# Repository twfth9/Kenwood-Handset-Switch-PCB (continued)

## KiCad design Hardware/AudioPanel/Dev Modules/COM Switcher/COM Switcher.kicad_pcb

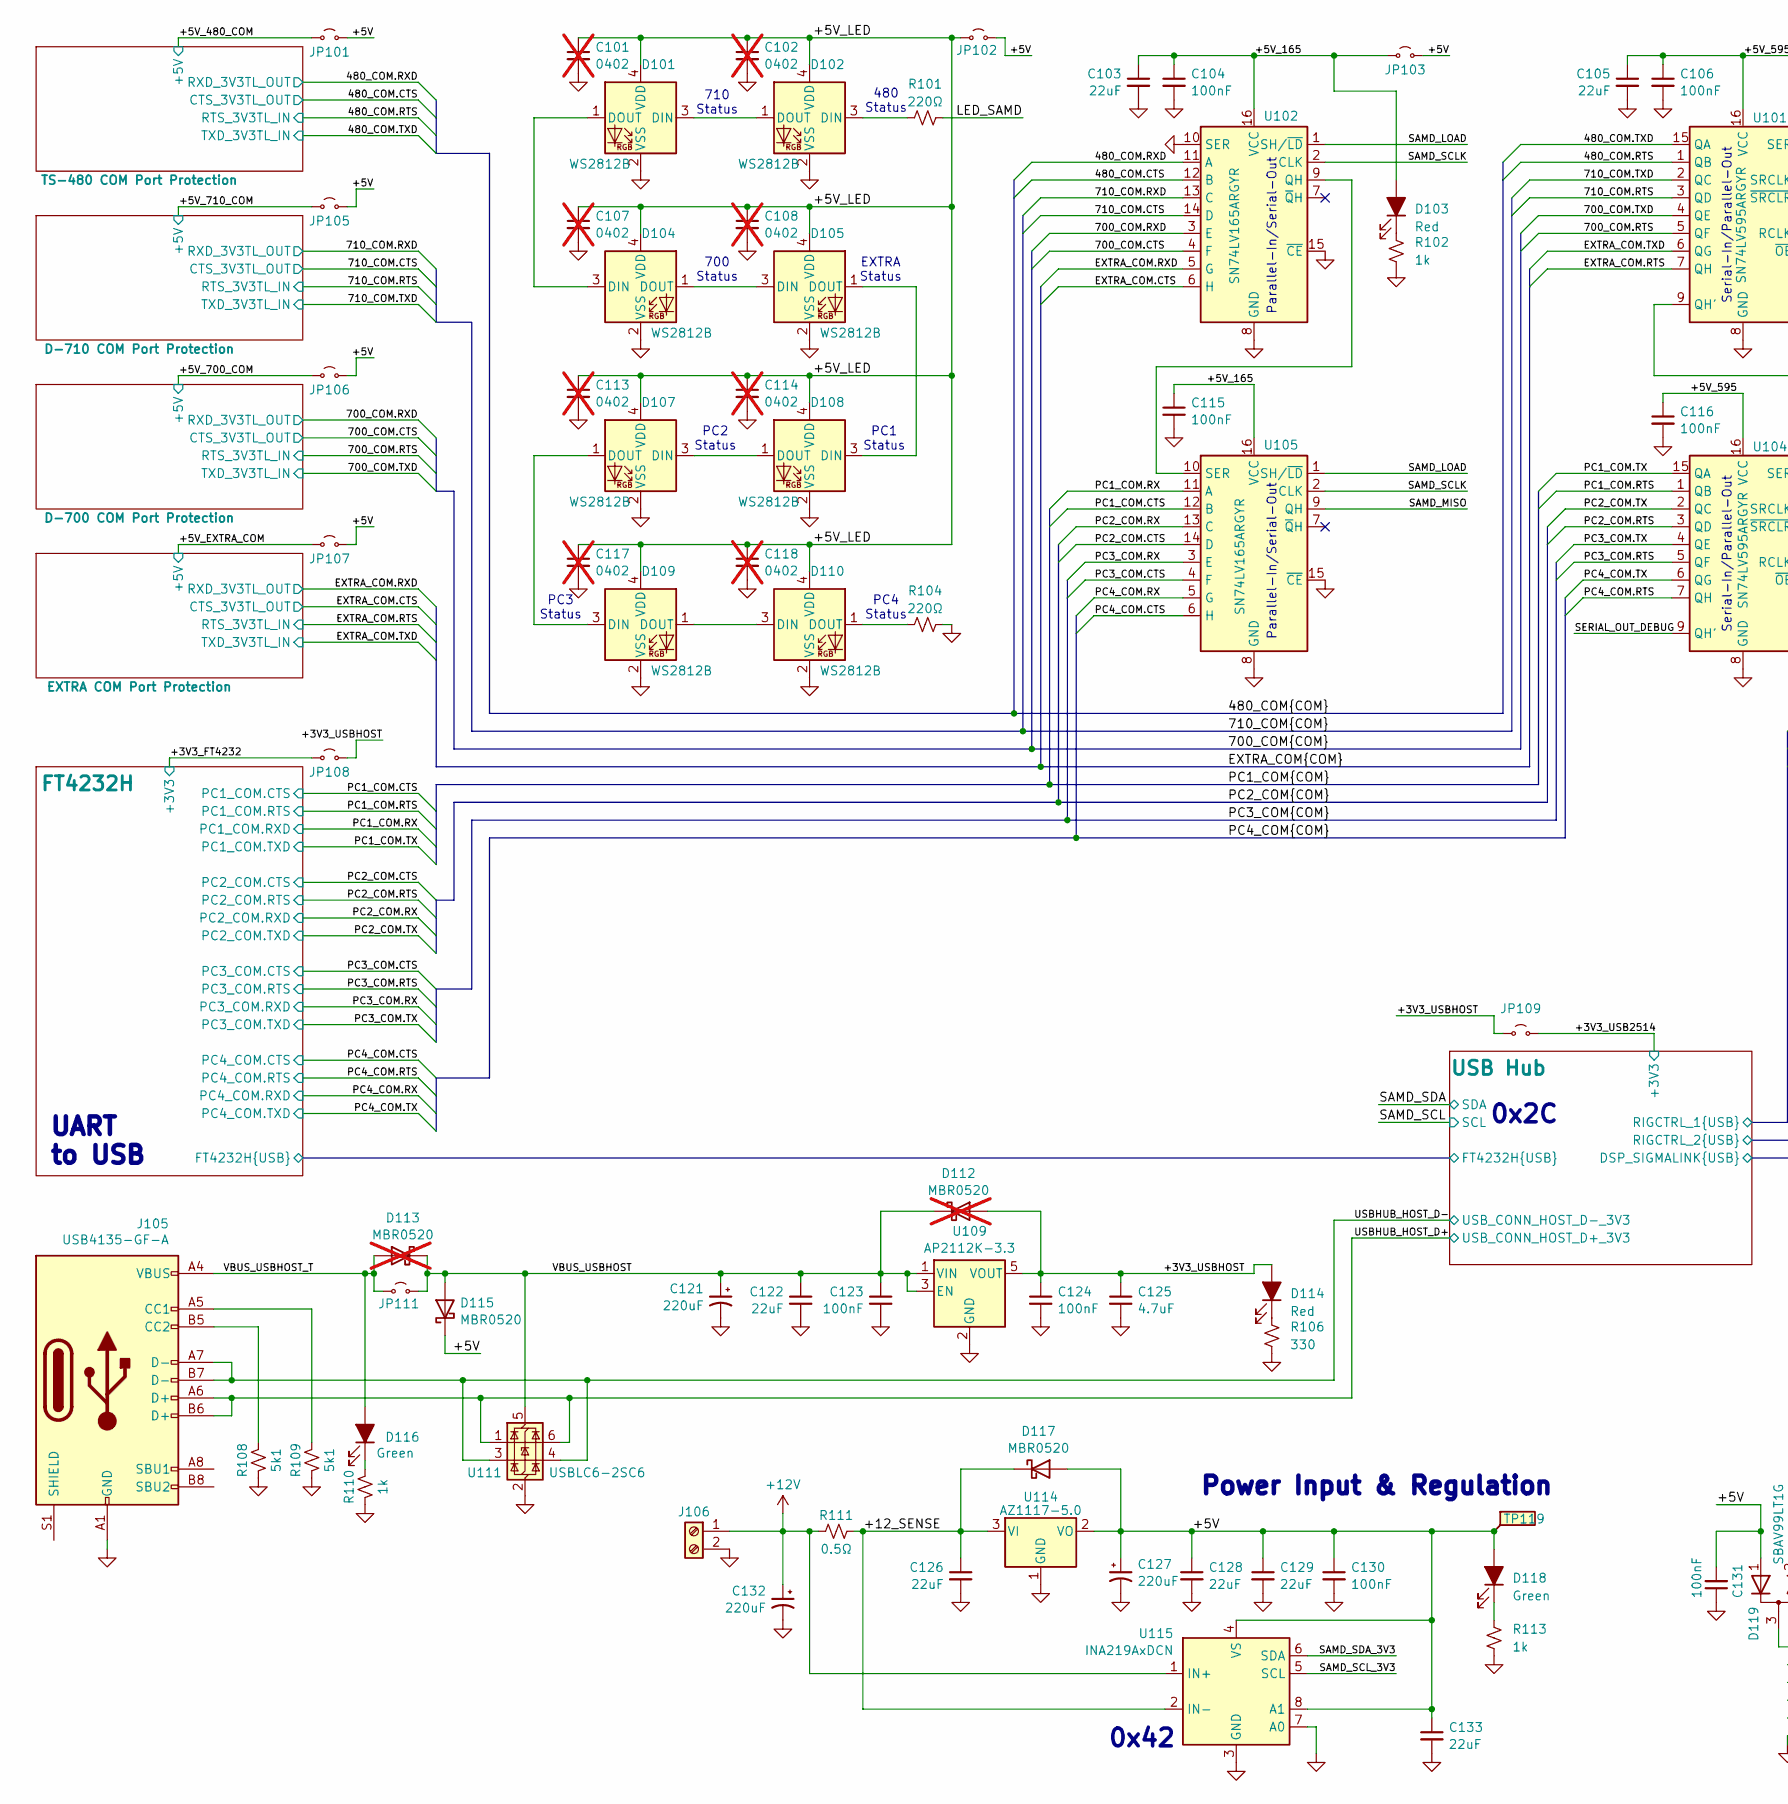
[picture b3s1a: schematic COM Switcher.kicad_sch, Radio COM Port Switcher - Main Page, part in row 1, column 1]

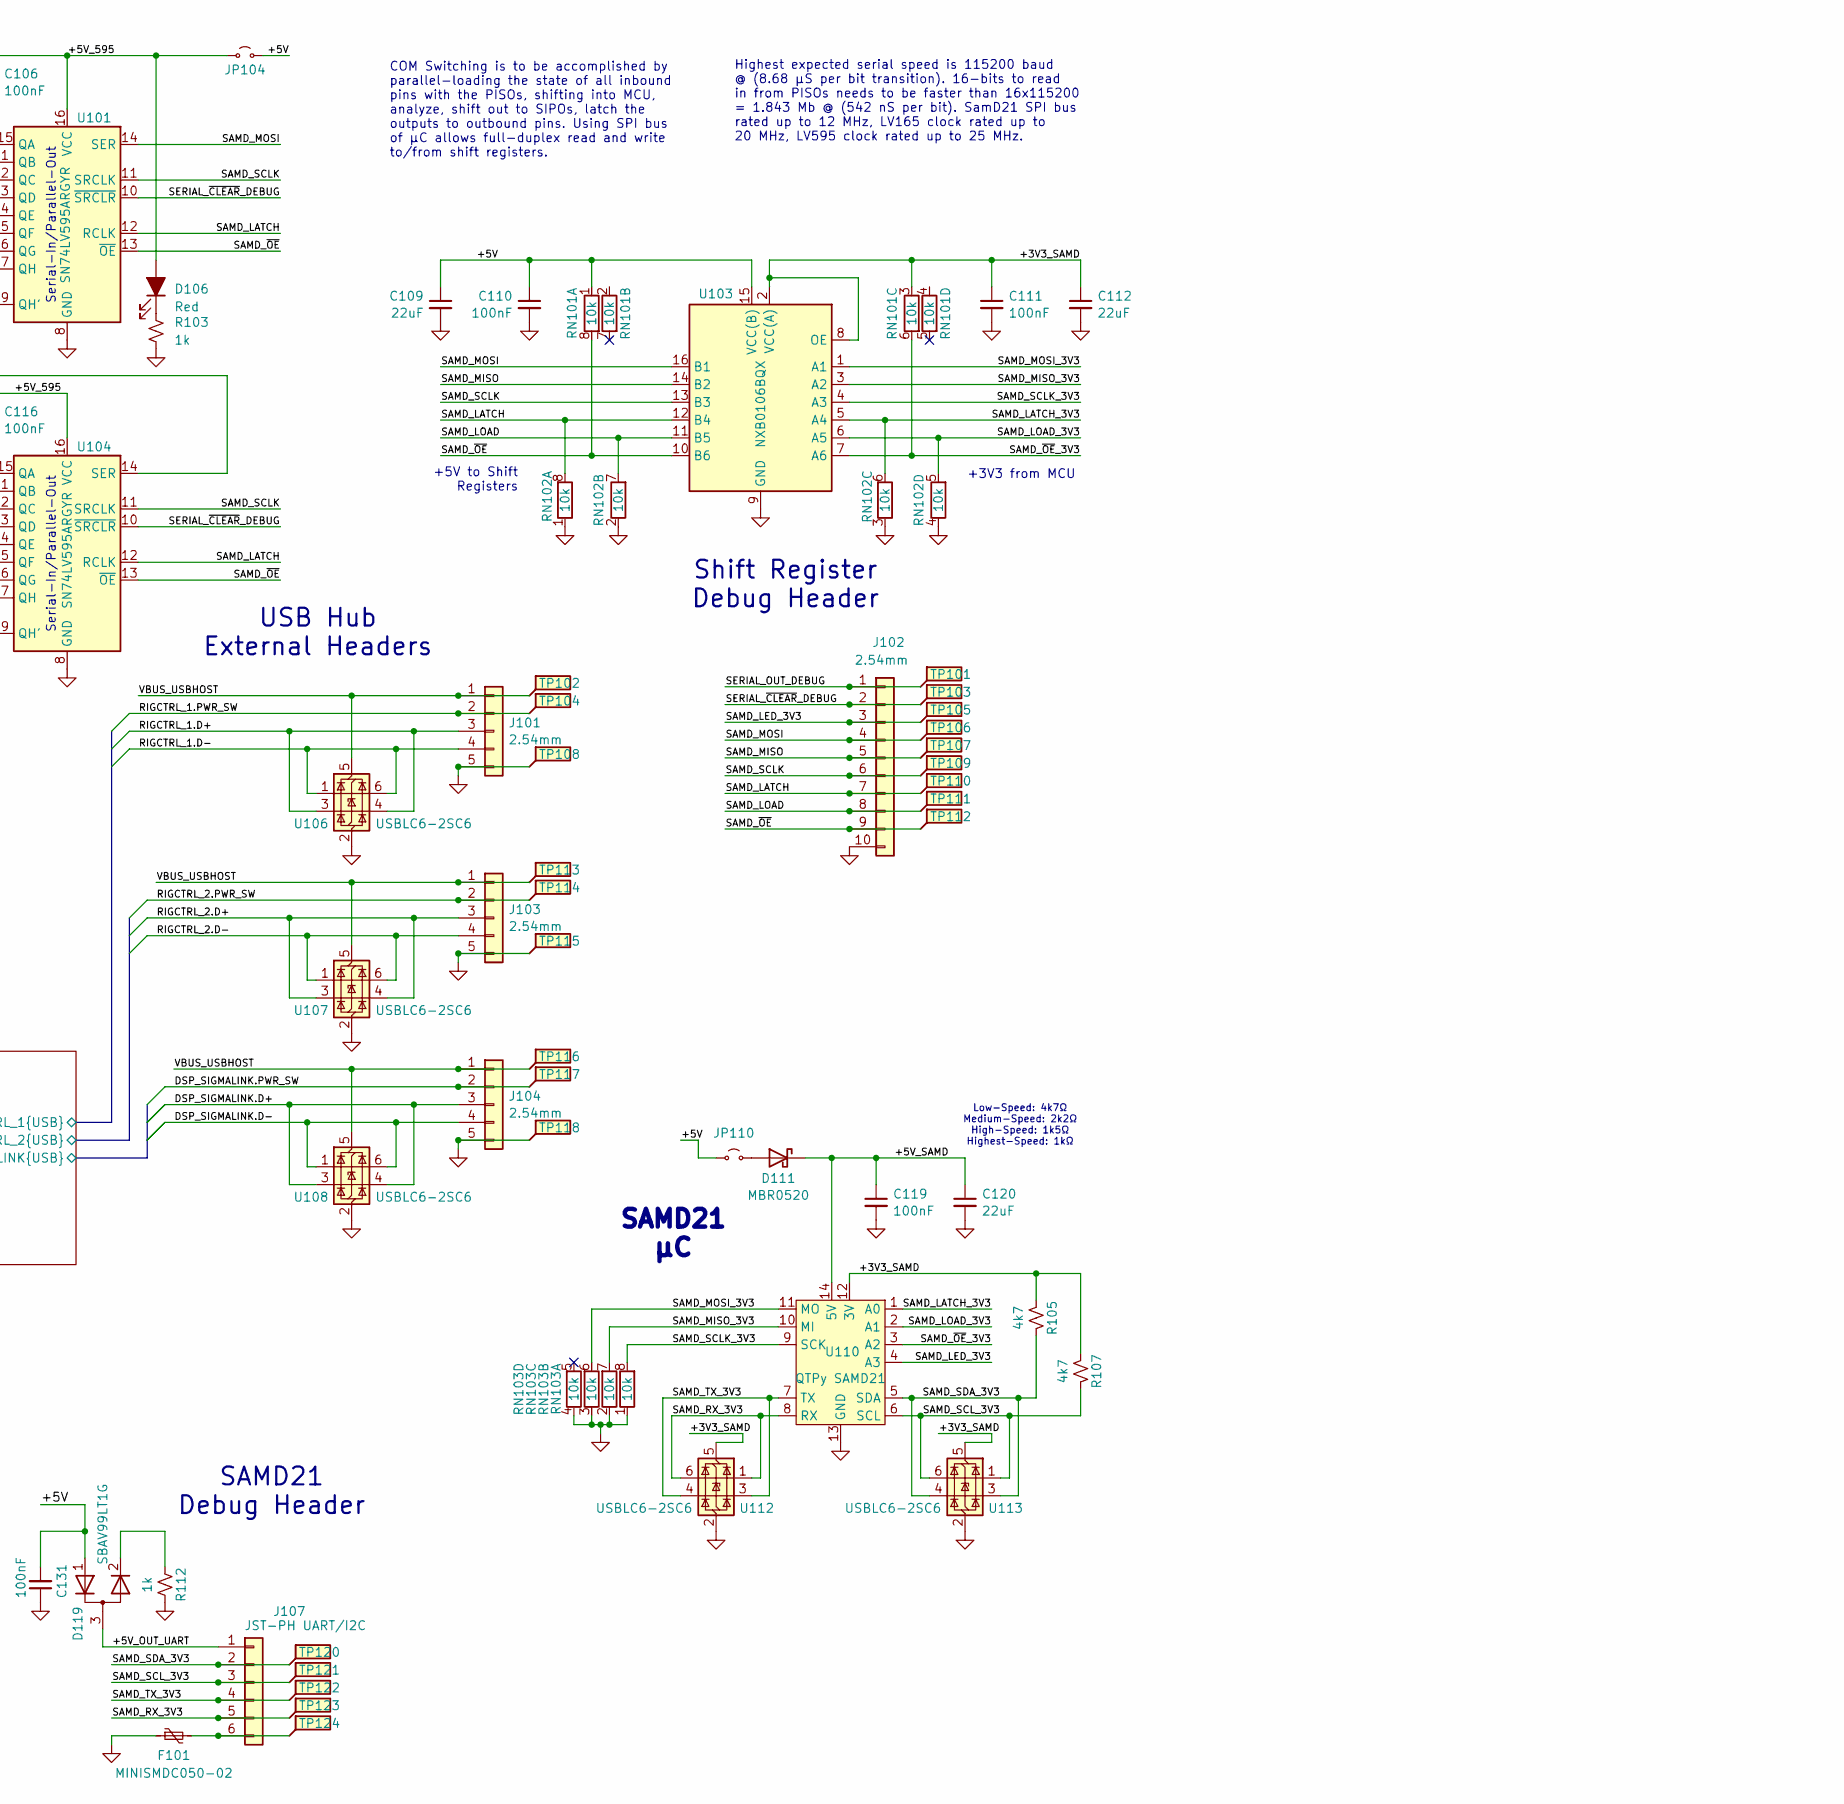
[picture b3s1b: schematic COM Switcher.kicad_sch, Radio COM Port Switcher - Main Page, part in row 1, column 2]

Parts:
C101, C102, C107, C108, C113, C114, C117, C118: 0402; Worthington_C_0402; not fitted
C103, C105, C109, C112, C120, C122, C126, C128, C129, C133: 22uF; Worthington_C_0603
C104, C106, C110, C111, C115, C116, C119, C123, C124, C130, C131: 100nF; Worthington_C_0402
C121, C127, C132: 220uF; CP_Elec_6.3x7.7
C125: 4.7uF; Worthington_C_0402
D101, D102, D104, D105, D107, D108, D109, D110: WS2812B; LED_WS2812B-2020_PLCC4_2.0x2.0mm
D103, D106: Red; Worthington_LED_0603; DigiKey Part Number 732-5016-ND
D111, D115, D117: MBR0520; D_SOD-123
D112, D113: MBR0520; D_SOD-123; not fitted
D114: Red; LED_D5.0mm; DigiKey Part Number 732-5016-ND
D116, D118: Green; LED_D5.0mm; DigiKey Part Number 732-5016-ND
D119: SBAV99LT1G; SOT-23
F101: MINISMDC050-02; Fuse_0805_2012Metric
J101, J103, J104: 2.54mm; JST_PH_S5B-PH-K_1x05_P2.00mm_Horizontal
J102: 2.54mm; PinHeader_1x10_P2.54mm_Vertical
J105: USB4135-GF-A; USB_C_Receptacle_GCT_USB4105-xx-A_16P_TopMnt_Horizontal
J106: Screw_Terminal_01x02; TerminalBlock_Phoenix_MKDS-1,5-2_1x02_P5.00mm_Horizontal
J107: JST-PH UART/I2C; JST_PH_S6B-PH-K_1x06_P2.00mm_Horizontal
JP101, JP102, JP103, JP104, JP105, JP106, JP107, JP108, JP109, JP110, JP111: Jumper_2_Small_Open; SolderJumper-2_P1.3mm_Open_Pad1.0x1.5mm
R101, R104: 220Ω; Worthington_R_0402
R102, R103, R113: 1k; Worthington_R_0402; DigiKey Part Number 311-510HRCT-ND
R105, R107: 4k7; Worthington_R_0402
R106: 330; Worthington_R_0402; DigiKey Part Number 311-510HRCT-ND
R108, R109: 5k1; Worthington_R_0402
R110, R112: 1k; Worthington_R_0402
R111: 0.5Ω; R_1206_3216Metric
RN101, RN102, RN103: 10k; RES_ARRAY_4RES_0804
TP101, TP102, TP103, TP104, TP105, TP106, TP107, TP108, TP109, TP110, TP111, TP112, TP113, TP114, TP115, TP116, TP117, TP118, TP119, TP120, TP121, TP122, TP123, TP124: TestPoint_Flag; KEYSTONE_5017
U101, U104: SN74LV595ARGYR; RGY16_2P55X2P05
U102, U105: SN74LV165ARGYR; RGY16_2P55X2P05
U103: NXB0106BQX; RGY16_2P55X2P05
U106, U107, U108, U111, U112, U113: USBLC6-2SC6; SOT-666
U109: AP2112K-3.3; SOT-23-5
U110: QTPy SAMD21; Py_QT_SAMD21_THT
U114: AZ1117-5.0; SOT-223-3_TabPin2
U115: INA219AxDCN; SOT-23-8

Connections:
+12V: C132.1, J106.1, R111.2, U115.1 (IN+)
/480_COM.CTS: U102.12 (B); also elsewhere on the board
/480_COM.RTS: U101.1 (QB); also elsewhere on the board
/480_COM.RXD: U102.11 (A); also elsewhere on the board
/480_COM.TXD: U101.15 (QA); also elsewhere on the board
/700_COM.CTS: U102.4 (F); also elsewhere on the board
/700_COM.RTS: U101.5 (QF); also elsewhere on the board
/700_COM.RXD: U102.3 (E); also elsewhere on the board
/700_COM.TXD: U101.4 (QE); also elsewhere on the board
/710_COM.CTS: U102.14 (D); also elsewhere on the board
/710_COM.RTS: U101.3 (QD); also elsewhere on the board
/710_COM.RXD: U102.13 (C); also elsewhere on the board
/710_COM.TXD: U101.2 (QC); also elsewhere on the board
/+3V3_FT4232: JP108.1 (A); also elsewhere on the board
/+3V3_SAMD: C111.1, C112.1, R105.1, R107.1, RN101.3, U103.2 (VCC(A)), U103.8 (OE), U110.12 (3V), U112.5 (VBUS), U113.5 (VBUS)
/+3V3_USB2514: JP109.2 (B); also elsewhere on the board
/+3V3_USBHOST: C124.1, C125.1, D112.2 (A), D114.2 (A), JP108.2 (B), JP109.1 (A), U109.5 (VOUT)
/+5V: C109.1, C110.1, C127.1, C128.1, C129.1, C130.1, C131.2, C133.1, D115.1 (K), D117.2 (A), D118.2 (A), D119.1 (A), JP101.2 (B), JP102.1 (A), JP103.2 (B), JP104.2 (B), JP105.2 (B), JP106.2 (B), JP107.2 (B), JP110.2 (B), RN101.1 (4), TP119.1, U103.15 (VCC(B)), U114.2 (VO), U115.4 (VS), U115.8 (A1)
/+5V_165: C103.1, C104.1, C115.1, D103.2 (A), JP103.1 (A), U102.16 (VCC), U105.16 (VCC)
/+5V_480_COM: JP101.1 (A); also elsewhere on the board
/+5V_595: C105.1, C106.1, C116.1, D106.2 (A), JP104.1 (A), U101.16 (VCC), U104.16 (VCC)
/+5V_700_COM: JP106.1 (A); also elsewhere on the board
/+5V_710_COM: JP105.1 (A); also elsewhere on the board
/+5V_EXTRA_COM: JP107.1 (A); also elsewhere on the board
/+5V_LED: C101.1, C102.1, C107.1, C108.1, C113.1, C114.1, C117.1, C118.1, D101.4 (VDD), D102.4 (VDD), D104.4 (VDD), D105.4 (VDD), D107.4 (VDD), D108.4 (VDD), D109.4 (VDD), D110.4 (VDD), JP102.2 (B)
/+5V_OUT_UART: D119.3 (common), J107.1
/+5V_SAMD: C119.1, C120.1, D111.1 (K), U110.14 (5V)
/+12_SENSE: C126.1, D117.1 (K), R111.1, U114.3 (VI), U115.2 (IN-)
/EXTRA_COM.CTS: U102.6 (H); also elsewhere on the board
/EXTRA_COM.RTS: U101.7 (QH); also elsewhere on the board
/EXTRA_COM.RXD: U102.5 (G); also elsewhere on the board
/EXTRA_COM.TXD: U101.6 (QG); also elsewhere on the board
/LED_SAMD: R101.2
/PC1_COM.CTS: U105.12 (B); also elsewhere on the board
/PC1_COM.RTS: U104.1 (QB); also elsewhere on the board
/PC1_COM.RX: U105.11 (A); also elsewhere on the board
/PC1_COM.TX: U104.15 (QA); also elsewhere on the board
/PC2_COM.CTS: U105.14 (D); also elsewhere on the board
/PC2_COM.RTS: U104.3 (QD); also elsewhere on the board
/PC2_COM.RX: U105.13 (C); also elsewhere on the board
/PC2_COM.TX: U104.2 (QC); also elsewhere on the board
/PC3_COM.CTS: U105.4 (F); also elsewhere on the board
/PC3_COM.RTS: U104.5 (QF); also elsewhere on the board
/PC3_COM.RX: U105.3 (E); also elsewhere on the board
/PC3_COM.TX: U104.4 (QE); also elsewhere on the board
/PC4_COM.CTS: U105.6 (H); also elsewhere on the board
/PC4_COM.RTS: U104.7 (QH); also elsewhere on the board
/PC4_COM.RX: U105.5 (G); also elsewhere on the board
/PC4_COM.TX: U104.6 (QG); also elsewhere on the board
/SAMD_LATCH: J102.7, RN102.8, TP110.1, U101.12 (RCLK), U103.12 (B4), U104.12 (RCLK)
/SAMD_LATCH_3V3: RN102.6, U103.5 (A4), U110.1 (A0)
/SAMD_LED_3V3: J102.3, TP105.1, U110.4 (A3)
/SAMD_LOAD: J102.8, RN102.7 (5), TP111.1, U102.1 (SH/~LD), U103.11 (B5), U105.1 (SH/~LD)
/SAMD_LOAD_3V3: RN102.5, U103.6 (A5), U110.2 (A1)
/SAMD_MISO: J102.5, TP107.1, U103.14 (B2), U105.9 (QH)
/SAMD_MISO_3V3: RN103.7 (5), U103.3 (A2), U110.10 (MI)
/SAMD_MOSI: J102.4, TP106.1, U101.14 (SER), U103.16 (B1)
/SAMD_MOSI_3V3: RN103.6, U103.1 (A1), U110.11 (MO)
/SAMD_RX_3V3: J107.5, TP123.1, U110.8 (RX), U112.1 (I/O1), U112.6 (I/O1)
/SAMD_SCLK: J102.6, TP109.1, U101.11 (SRCLK), U102.2 (CLK), U103.13 (B3), U104.11 (SRCLK), U105.2 (CLK)
/SAMD_SCLK_3V3: RN103.8, U103.4 (A3), U110.9 (SCK)
/SAMD_SCL_3V3: J107.3, R107.2, TP121.1, U110.6 (SCL), U113.1 (I/O1), U113.6 (I/O1), U115.5 (SCL)
/SAMD_SDA_3V3: J107.2, R105.2, TP120.1, U110.5 (SDA), U113.3 (I/O2), U113.4 (I/O2), U115.6 (SDA)
/SAMD_TX_3V3: J107.4, TP122.1, U110.7 (TX), U112.3 (I/O2), U112.4 (I/O2)
/SAMD_~OE: J102.9, RN101.8, TP112.1, U101.13 (~OE), U103.10 (B6), U104.13 (~OE)
/SAMD_~OE_3V3: RN101.6, U103.7 (A6), U110.3 (A2)
/SERIAL_OUT_DEBUG: J102.1, TP101.1, U104.9 (QH')
/SERIAL_~CLEAR_DEBUG: J102.2, TP103.1, U101.10 (~SRCLR), U104.10 (~SRCLR)
/USB Hub/DSP_SIGMALINK.D+: J104.3, U108.3 (I/O2), U108.4 (I/O2); also elsewhere on the board
/USB Hub/DSP_SIGMALINK.D-: J104.4, U108.1 (I/O1), U108.6 (I/O1); also elsewhere on the board
/USB Hub/DSP_SIGMALINK.PWR_SW: J104.2, TP117.1; also elsewhere on the board
/USB Hub/RIGCTRL_1.D+: J101.3, U106.3 (I/O2), U106.4 (I/O2)
/USB Hub/RIGCTRL_1.D-: J101.4, U106.1 (I/O1), U106.6 (I/O1); also elsewhere on the board
/USB Hub/RIGCTRL_1.PWR_SW: J101.2, TP104.1; also elsewhere on the board
/USB Hub/RIGCTRL_2.D+: J103.3, U107.3 (I/O2), U107.4 (I/O2); also elsewhere on the board
/USB Hub/RIGCTRL_2.D-: J103.4, U107.1 (I/O1), U107.6 (I/O1); also elsewhere on the board
/USB Hub/RIGCTRL_2.PWR_SW: J103.2, TP114.1; also elsewhere on the board
/USBHUB_HOST_D+: J105.A6 (D+), J105.B6 (D+), U111.1 (I/O1), U111.6 (I/O1); also elsewhere on the board
/USBHUB_HOST_D-: J105.A7 (D-), J105.B7 (D-), U111.3 (I/O2), U111.4 (I/O2); also elsewhere on the board
/VBUS_USBHOST: C121.1, C122.1, C123.1, D112.1 (K), D113.1 (K), D115.2 (A), J101.1, J103.1, J104.1, JP111.1 (A), TP102.1, TP113.1, TP116.1, U106.5 (VBUS), U107.5 (VBUS), U108.5 (VBUS), U109.1 (VIN), U109.3 (EN), U111.5 (VBUS)
/VBUS_USBHOST_T: D113.2 (A), D116.2 (A), J105.A4 (VBUS), J105.A9 (VBUS), J105.B4 (VBUS), J105.B9 (VBUS), JP111.2 (B)
GND: C101.2, C102.2, C103.2, C104.2, C105.2, C106.2, C107.2, C108.2, C109.2, C110.2, C111.2, C112.2, C113.2, C114.2, C115.2, C116.2, C117.2, C118.2, C119.2, C120.2, C121.2, C122.2, C123.2, C124.2, C125.2, C126.2, C127.2, C128.2, C129.2, C130.2, C131.1, C132.2, C133.2, D101.2 (VSS), D102.2 (VSS), D104.2 (VSS), D105.2 (VSS), D107.2 (VSS), D108.2 (VSS), D109.2 (VSS), D110.2 (VSS), F101.1, J101.5, J102.10, J103.5, J104.5, J105.A1 (GND), J105.A12 (GND), J105.B1 (GND), J105.B12 (GND), J106.2, R102.1, R103.1, R104.2, R106.1, R108.1, R109.1, R110.1, R112.1, R113.1, RN102.1 (4), RN102.2, RN102.3, RN102.4, RN103.1 (4), RN103.2, RN103.3, RN103.4, TP108.1, TP115.1, TP118.1, U101.8 (GND), U101.17 (GND), U102.8 (GND), U102.10 (SER), U102.15 (~CE), U102.17 (GND), U103.9 (GND), U103.17 (GND), U104.8 (GND), U104.17 (GND), U105.8 (GND), U105.15 (~CE), U105.17 (GND), U106.2 (GND), U107.2 (GND), U108.2 (GND), U109.2 (GND), U110.13 (GND), U111.2 (GND), U112.2 (GND), U113.2 (GND), U114.1 (GND), U115.3 (GND), U115.7 (A0); also elsewhere on the board
unnamed: D101.3 (DIN), D102.1 (DOUT)
unnamed: D101.1 (DOUT), D104.3 (DIN)
unnamed: D102.3 (DIN), R101.1
unnamed: D103.1 (K), R102.2
unnamed: D104.1 (DOUT), D105.3 (DIN)
unnamed: D105.1 (DOUT), D108.3 (DIN)
unnamed: D106.1 (K), R103.2
unnamed: D107.3 (DIN), D108.1 (DOUT)
unnamed: D107.1 (DOUT), D109.3 (DIN)
unnamed: D109.1 (DOUT), D110.3 (DIN)
unnamed: D110.1 (DOUT), R104.1
unnamed: D111.2 (A), JP110.1 (A)
unnamed: D114.1 (K), R106.2
unnamed: D116.1 (K), R110.2
unnamed: D118.1 (K), R113.2
unnamed: D119.2 (K), R112.2
unnamed: J105.A5 (CC1), R109.2
unnamed: J105.B5 (CC2), R108.2
unnamed: F101.2, J107.6, TP124.1
unnamed: U101.9 (QH'), U104.14 (SER)
unnamed: U102.9 (QH), U105.10 (SER)

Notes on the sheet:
PC1 Status
COM Switching is to be accomplished by parallel-loading the state of all inbound pins with the PISOs, shifting into MCU, analyze, shift out to SIPOs, latch the outputs to outbound pins. Using SPI bus of µC allows full-duplex read and write to/from shift registers.
UART to USB
SAMD21 µC
USB Hub External Headers
Parallel-In/Serial-Out
480 Status
SAMD21 Debug Header
700 Status
710 Status
PC4 Status
Shift Register Debug Header
Serial-In/Parallel-Out
Low-Speed: 4k7Ω Medium-Speed: 2k2Ω High-Speed: 1k5Ω Highest-Speed: 1kΩ
Power Input & Regulation
+5V to Shift Registers
0x42
EXTRA Status
0x2C
PC2 Status
+3V3 from MCU
PC3 Status
Highest expected serial speed is 115200 baud @ (8.68 µS per bit transition). 16-bits to read in from PISOs needs to be faster than 16x115200 = 1.843 Mb @ (542 nS per bit). SamD21 SPI bus rated up to 12 MHz, LV165 clock rated up to 20 MHz, LV595 clock rated up to 25 MHz.

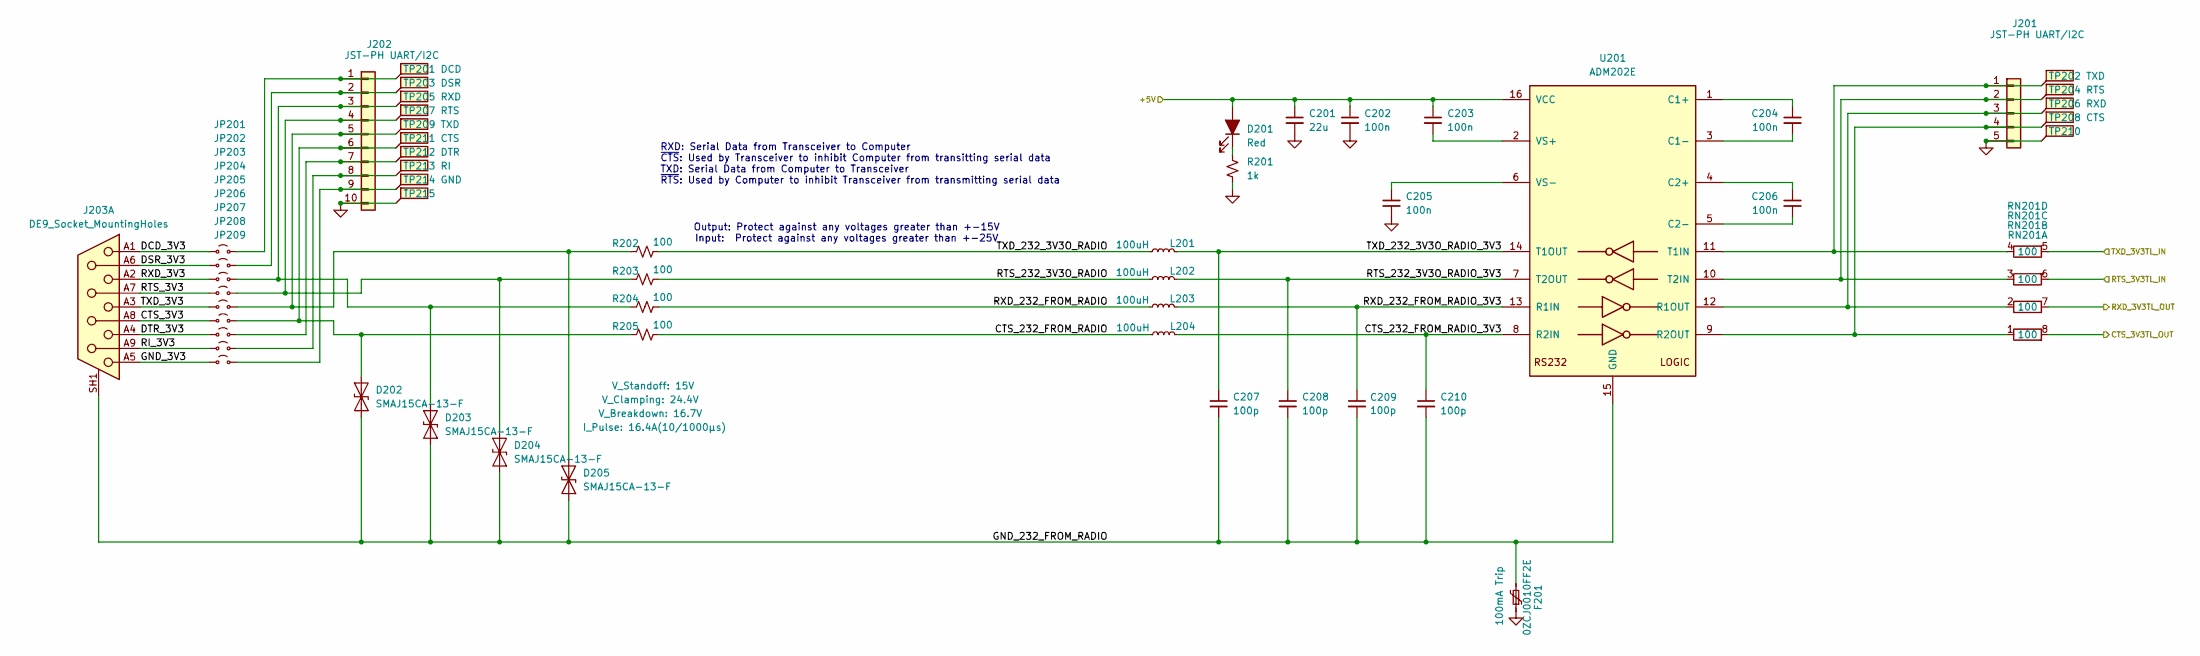
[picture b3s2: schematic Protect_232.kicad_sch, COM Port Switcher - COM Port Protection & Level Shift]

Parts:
C201: 22u; Worthington_C_0603
C202, C203, C204, C205, C206: 100n; Worthington_C_0402
C207, C208, C209, C210: 100p; Worthington_C_0402
D201: Red; Worthington_LED_0603; DigiKey Part Number 732-5016-ND
D202, D203, D204, D205: SMAJ15CA-13-F; D_SMA
F201: 0ZCJ0010FF2E; Fuse_1206_3216Metric
J201: JST-PH UART/I2C; PinHeader_1x05_P2.54mm_Vertical
J202: JST-PH UART/I2C; PinHeader_1x10_P2.54mm_Vertical
J203: DE9_Socket_MountingHoles; NORCOMP_189-009-513R571
JP201, JP202, JP203, JP204, JP205, JP206, JP207, JP208, JP209: Jumper_2_Small_Open; SolderJumper-2_P1.3mm_Open_Pad1.0x1.5mm
L201, L202, L203, L204: 100uH; Worthington_L_0805
R201: 1k; Worthington_R_0402; DigiKey Part Number 311-510HRCT-ND
R202, R203, R204, R205: 100; Worthington_R_0402
RN201: 100; RES_ARRAY_4RES_0804
TP201: DCD; KEYSTONE_5017
TP202, TP209: TXD; KEYSTONE_5017
TP203: DSR; KEYSTONE_5017
TP204, TP207: RTS; KEYSTONE_5017
TP205, TP206: RXD; KEYSTONE_5017
TP208, TP211: CTS; KEYSTONE_5017
TP210, TP215: KEYSTONE_5017
TP212: DTR; KEYSTONE_5017
TP213: RI; KEYSTONE_5017
TP214: GND; KEYSTONE_5017
U201: ADM202E; SOIC-16_3.9x9.9mm_P1.27mm

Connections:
/700_COM.CTS: RN201.8; also elsewhere on the board
/700_COM.RTS: RN201.6; also elsewhere on the board
/700_COM.RXD: RN201.7 (5); also elsewhere on the board
/700_COM.TXD: RN201.5; also elsewhere on the board
/+5V_700_COM: C201.1, C202.1, C203.1, D201.2 (A), U201.16 (VCC); also elsewhere on the board
/D-700 COM Port Protection/CTS_3V3: J203.A8, JP206.1 (A)
/D-700 COM Port Protection/CTS_232_FROM_RADIO: L204.2, R205.2
/D-700 COM Port Protection/CTS_232_FROM_RADIO_3V3: C210.1, L204.1, U201.8 (R2IN)
/D-700 COM Port Protection/DCD_3V3: J203.A1, JP201.1 (A)
/D-700 COM Port Protection/DSR_3V3: J203.A6, JP202.1 (A)
/D-700 COM Port Protection/DTR_3V3: J203.A4, JP207.1 (A)
/D-700 COM Port Protection/GND_3V3: J203.A5, JP209.1 (A)
/D-700 COM Port Protection/GND_232_FROM_RADIO: C207.2, C208.2, C209.2, C210.2, D202.1 (A1), D203.1 (A1), D204.1 (A1), D205.1 (A1), F201.2, J203.SH1 (PAD), J203.SH2 (PAD), U201.15 (GND)
/D-700 COM Port Protection/RI_3V3: J203.A9, JP208.1 (A)
/D-700 COM Port Protection/RTS_3V3: J203.A7, JP204.1 (A)
/D-700 COM Port Protection/RTS_232_3V3O_RADIO: L202.2, R203.2
/D-700 COM Port Protection/RTS_232_3V3O_RADIO_3V3: C208.1, L202.1, U201.7 (T2OUT)
/D-700 COM Port Protection/RXD_3V3: J203.A2, JP203.1 (A)
/D-700 COM Port Protection/RXD_232_FROM_RADIO: L203.2, R204.2
/D-700 COM Port Protection/RXD_232_FROM_RADIO_3V3: C209.1, L203.1, U201.13 (R1IN)
/D-700 COM Port Protection/TXD_3V3: J203.A3, JP205.1 (A)
/D-700 COM Port Protection/TXD_232_3V3O_RADIO: L201.2, R202.2
/D-700 COM Port Protection/TXD_232_3V3O_RADIO_3V3: C207.1, L201.1, U201.14 (T1OUT)
/EXTRA COM Port Protection/CTS_3V3: J203.B8; also elsewhere on the board
/EXTRA COM Port Protection/DCD_3V3: J203.B1; also elsewhere on the board
/EXTRA COM Port Protection/DSR_3V3: J203.B6; also elsewhere on the board
/EXTRA COM Port Protection/DTR_3V3: J203.B4; also elsewhere on the board
/EXTRA COM Port Protection/GND_3V3: J203.B5; also elsewhere on the board
/EXTRA COM Port Protection/GND_232_FROM_RADIO: J203.SH3 (PAD), J203.SH4 (PAD); also elsewhere on the board
/EXTRA COM Port Protection/RI_3V3: J203.B9; also elsewhere on the board
/EXTRA COM Port Protection/RTS_3V3: J203.B7; also elsewhere on the board
/EXTRA COM Port Protection/RXD_3V3: J203.B2; also elsewhere on the board
/EXTRA COM Port Protection/TXD_3V3: J203.B3; also elsewhere on the board
GND: C201.2, C202.2, C205.2, F201.1, J201.5, J202.10, R201.1, TP210.1, TP215.1; also elsewhere on the board
unnamed: D201.1 (K), R201.2
unnamed: D202.2 (A2), J202.6, JP206.2 (B), R205.1, TP211.1
unnamed: D203.2 (A2), J202.3, JP203.2 (B), R204.1, TP205.1
unnamed: D204.2 (A2), J202.4, JP204.2 (B), R203.1, TP207.1
unnamed: D205.2 (A2), J202.5, JP205.2 (B), R202.1, TP209.1
unnamed: J201.1, RN201.4, TP202.1, U201.11 (T1IN)
unnamed: J201.2, RN201.3, TP204.1, U201.10 (T2IN)
unnamed: J201.3, RN201.2, TP206.1, U201.12 (R1OUT)
unnamed: J201.4, RN201.1 (4), TP208.1, U201.9 (R2OUT)
unnamed: J202.1, JP201.2 (B), TP201.1
unnamed: J202.2, JP202.2 (B), TP203.1
unnamed: J202.7, JP207.2 (B), TP212.1
unnamed: J202.8, JP208.2 (B), TP213.1
unnamed: J202.9, JP209.2 (B), TP214.1
unnamed: C204.1, U201.1 (C1+)
unnamed: C204.2, U201.3 (C1-)
unnamed: C206.1, U201.4 (C2+)
unnamed: C206.2, U201.5 (C2-)
unnamed: C203.2, U201.2 (VS+)
unnamed: C205.1, U201.6 (VS-)

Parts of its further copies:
C301, C401, C501: 22u; Worthington_C_0603
C302, C303, C304, C305, C306, C402, C403, C404, C405, C406, C502, C503, C504, C505, C506: 100n; Worthington_C_0402
C307, C309, C407, C408, C409, C410, C507, C508, C509, C510: 100p; Worthington_C_0402
D301, D401, D501: Red; Worthington_LED_0603; DigiKey Part Number 732-5016-ND
D302, D303, D304, D305, D402, D403, D404, D405, D502, D503, D504, D505: SMAJ15CA-13-F; D_SMA
F301, F401, F501: 0ZCJ0010FF2E; Fuse_1206_3216Metric
J301, J401, J501: JST-PH UART/I2C; PinHeader_1x05_P2.54mm_Vertical
J302, J402, J502: JST-PH UART/I2C; PinHeader_1x10_P2.54mm_Vertical
J303: DE9_Socket_MountingHoles; NORCOMP_189-009-513R571
JP301, JP302, JP303, JP304, JP305, JP306, JP307, JP308, JP309, JP401, JP402, JP403, JP404, JP405, JP406, JP407, JP408, JP409, JP501, JP502, JP503, JP504, JP505, JP506, JP507, JP508, JP509: Jumper_2_Small_Open; SolderJumper-2_P1.3mm_Open_Pad1.0x1.5mm
L301, L302, L303, L304, L401, L402, L403, L404, L501, L502, L503, L504: 100uH; Worthington_L_0805
R301, R401, R501: 1k; Worthington_R_0402; DigiKey Part Number 311-510HRCT-ND
R302, R303, R304, R305, R402, R403, R404, R405, R502, R503, R504, R505: 100; Worthington_R_0402
RN301, RN401, RN501: 100; RES_ARRAY_4RES_0804
TP301, TP401, TP501: DCD; KEYSTONE_5017
TP302, TP309, TP402, TP409, TP502, TP509: TXD; KEYSTONE_5017
TP303, TP403, TP503: DSR; KEYSTONE_5017
TP304, TP307, TP404, TP407, TP504, TP507: RTS; KEYSTONE_5017
TP305, TP306, TP405, TP406, TP505, TP506: RXD; KEYSTONE_5017
TP308, TP311, TP408, TP411, TP508, TP511: CTS; KEYSTONE_5017
TP310, TP315, TP410, TP415, TP510, TP515: KEYSTONE_5017
TP312, TP412, TP512: DTR; KEYSTONE_5017
TP313, TP413, TP513: RI; KEYSTONE_5017
TP314, TP414, TP514: GND; KEYSTONE_5017
U301, U401, U501: ADM202E; SOIC-16_3.9x9.9mm_P1.27mm

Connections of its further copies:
/480_COM.CTS: RN501.8; also elsewhere on the board
/480_COM.RTS: RN501.6; also elsewhere on the board
/480_COM.RXD: RN501.7 (5); also elsewhere on the board
/480_COM.TXD: RN501.5; also elsewhere on the board
/710_COM.CTS: RN301.8; also elsewhere on the board
/710_COM.RTS: RN301.6; also elsewhere on the board
/710_COM.RXD: RN301.7 (5); also elsewhere on the board
/710_COM.TXD: RN301.5; also elsewhere on the board
/+5V_480_COM: C501.1, C502.1, C503.1, D501.2 (A), U501.16 (VCC); also elsewhere on the board
/+5V_710_COM: C301.1, C302.1, C303.1, D301.2 (A), U301.16 (VCC); also elsewhere on the board
/+5V_EXTRA_COM: C401.1, C402.1, C403.1, D401.2 (A), U401.16 (VCC); also elsewhere on the board
/D-710 COM Port Protection/CTS_3V3: J303.B8, JP306.1 (A)
/D-710 COM Port Protection/CTS_232_FROM_RADIO: L304.2, R305.2
/D-710 COM Port Protection/CTS_232_FROM_RADIO_3V3: L304.1, U301.8 (R2IN); also elsewhere on the board
/D-710 COM Port Protection/DCD_3V3: J303.B1, JP301.1 (A)
/D-710 COM Port Protection/DSR_3V3: J303.B6, JP302.1 (A)
/D-710 COM Port Protection/DTR_3V3: J303.B4, JP307.1 (A)
/D-710 COM Port Protection/GND_3V3: J303.B5, JP309.1 (A)
/D-710 COM Port Protection/GND_232_FROM_RADIO: C307.2, C309.2, D302.1 (A1), D303.1 (A1), D304.1 (A1), D305.1 (A1), F301.2, J303.SH3 (PAD), J303.SH4 (PAD), U301.15 (GND); also elsewhere on the board
/D-710 COM Port Protection/RI_3V3: J303.B9, JP308.1 (A)
/D-710 COM Port Protection/RTS_3V3: J303.B7, JP304.1 (A)
/D-710 COM Port Protection/RTS_232_3V3O_RADIO: L302.2, R303.2
/D-710 COM Port Protection/RTS_232_3V3O_RADIO_3V3: L302.1, U301.7 (T2OUT); also elsewhere on the board
/D-710 COM Port Protection/RXD_3V3: J303.B2, JP303.1 (A)
/D-710 COM Port Protection/RXD_232_FROM_RADIO: L303.2, R304.2
/D-710 COM Port Protection/RXD_232_FROM_RADIO_3V3: C309.1, L303.1, U301.13 (R1IN)
/D-710 COM Port Protection/TXD_3V3: J303.B3, JP305.1 (A)
/D-710 COM Port Protection/TXD_232_3V3O_RADIO: L301.2, R302.2
/D-710 COM Port Protection/TXD_232_3V3O_RADIO_3V3: C307.1, L301.1, U301.14 (T1OUT)
/EXTRA COM Port Protection/CTS_3V3: JP406.1 (A); also elsewhere on the board
/EXTRA COM Port Protection/CTS_232_FROM_RADIO: L404.2, R405.2
/EXTRA COM Port Protection/CTS_232_FROM_RADIO_3V3: C410.1, L404.1, U401.8 (R2IN)
/EXTRA COM Port Protection/DCD_3V3: JP401.1 (A); also elsewhere on the board
/EXTRA COM Port Protection/DSR_3V3: JP402.1 (A); also elsewhere on the board
/EXTRA COM Port Protection/DTR_3V3: JP407.1 (A); also elsewhere on the board
/EXTRA COM Port Protection/GND_3V3: JP409.1 (A); also elsewhere on the board
/EXTRA COM Port Protection/GND_232_FROM_RADIO: C407.2, C408.2, C409.2, C410.2, D402.1 (A1), D403.1 (A1), D404.1 (A1), D405.1 (A1), F401.2, U401.15 (GND); also elsewhere on the board
/EXTRA COM Port Protection/RI_3V3: JP408.1 (A); also elsewhere on the board
/EXTRA COM Port Protection/RTS_3V3: JP404.1 (A); also elsewhere on the board
/EXTRA COM Port Protection/RTS_232_3V3O_RADIO: L402.2, R403.2
/EXTRA COM Port Protection/RTS_232_3V3O_RADIO_3V3: C408.1, L402.1, U401.7 (T2OUT)
/EXTRA COM Port Protection/RXD_3V3: JP403.1 (A); also elsewhere on the board
/EXTRA COM Port Protection/RXD_232_FROM_RADIO: L403.2, R404.2
/EXTRA COM Port Protection/RXD_232_FROM_RADIO_3V3: C409.1, L403.1, U401.13 (R1IN)
/EXTRA COM Port Protection/TXD_3V3: JP405.1 (A); also elsewhere on the board
/EXTRA COM Port Protection/TXD_232_3V3O_RADIO: L401.2, R402.2
/EXTRA COM Port Protection/TXD_232_3V3O_RADIO_3V3: C407.1, L401.1, U401.14 (T1OUT)
/EXTRA_COM.CTS: RN401.8; also elsewhere on the board
/EXTRA_COM.RTS: RN401.6; also elsewhere on the board
/EXTRA_COM.RXD: RN401.7 (5); also elsewhere on the board
/EXTRA_COM.TXD: RN401.5; also elsewhere on the board
/TS-480 COM Port Protection/CTS_3V3: J303.A8, JP506.1 (A)
/TS-480 COM Port Protection/CTS_232_FROM_RADIO: L504.2, R505.2
/TS-480 COM Port Protection/CTS_232_FROM_RADIO_3V3: C510.1, L504.1, U501.8 (R2IN)
/TS-480 COM Port Protection/DCD_3V3: J303.A1, JP501.1 (A)
/TS-480 COM Port Protection/DSR_3V3: J303.A6, JP502.1 (A)
/TS-480 COM Port Protection/DTR_3V3: J303.A4, JP507.1 (A)
/TS-480 COM Port Protection/GND_3V3: J303.A5, JP509.1 (A)
/TS-480 COM Port Protection/GND_232_FROM_RADIO: C507.2, C508.2, C509.2, C510.2, D502.1 (A1), D503.1 (A1), D504.1 (A1), D505.1 (A1), F501.2, J303.SH1 (PAD), J303.SH2 (PAD), U501.15 (GND)
/TS-480 COM Port Protection/RI_3V3: J303.A9, JP508.1 (A)
/TS-480 COM Port Protection/RTS_3V3: J303.A7, JP504.1 (A)
/TS-480 COM Port Protection/RTS_232_3V3O_RADIO: L502.2, R503.2
/TS-480 COM Port Protection/RTS_232_3V3O_RADIO_3V3: C508.1, L502.1, U501.7 (T2OUT)
/TS-480 COM Port Protection/RXD_3V3: J303.A2, JP503.1 (A)
/TS-480 COM Port Protection/RXD_232_FROM_RADIO: L503.2, R504.2
/TS-480 COM Port Protection/RXD_232_FROM_RADIO_3V3: C509.1, L503.1, U501.13 (R1IN)
/TS-480 COM Port Protection/TXD_3V3: J303.A3, JP505.1 (A)
/TS-480 COM Port Protection/TXD_232_3V3O_RADIO: L501.2, R502.2
/TS-480 COM Port Protection/TXD_232_3V3O_RADIO_3V3: C507.1, L501.1, U501.14 (T1OUT)
GND: C301.2, C302.2, C305.2, C401.2, C402.2, C405.2, C501.2, C502.2, C505.2, F301.1, F401.1, F501.1, J301.5, J302.10, J401.5, J402.10, J501.5, J502.10, R301.1, R401.1, R501.1, TP310.1, TP315.1, TP410.1, TP415.1, TP510.1, TP515.1; also elsewhere on the board
unnamed: D301.1 (K), R301.2
unnamed: D302.2 (A2), J302.6, JP306.2 (B), R305.1, TP311.1
unnamed: D303.2 (A2), J302.3, JP303.2 (B), R304.1, TP305.1
unnamed: D304.2 (A2), J302.4, JP304.2 (B), R303.1, TP307.1
unnamed: D305.2 (A2), J302.5, JP305.2 (B), R302.1, TP309.1
unnamed: D401.1 (K), R401.2
unnamed: D402.2 (A2), J402.6, JP406.2 (B), R405.1, TP411.1
unnamed: D403.2 (A2), J402.3, JP403.2 (B), R404.1, TP405.1
unnamed: D404.2 (A2), J402.4, JP404.2 (B), R403.1, TP407.1
unnamed: D405.2 (A2), J402.5, JP405.2 (B), R402.1, TP409.1
unnamed: D501.1 (K), R501.2
unnamed: D502.2 (A2), J502.6, JP506.2 (B), R505.1, TP511.1
unnamed: D503.2 (A2), J502.3, JP503.2 (B), R504.1, TP505.1
unnamed: D504.2 (A2), J502.4, JP504.2 (B), R503.1, TP507.1
unnamed: D505.2 (A2), J502.5, JP505.2 (B), R502.1, TP509.1
unnamed: J301.1, RN301.4, TP302.1, U301.11 (T1IN)
unnamed: J301.2, RN301.3, TP304.1, U301.10 (T2IN)
unnamed: J301.3, RN301.2, TP306.1, U301.12 (R1OUT)
unnamed: J301.4, RN301.1 (4), TP308.1, U301.9 (R2OUT)
unnamed: J302.1, JP301.2 (B), TP301.1
unnamed: J302.2, JP302.2 (B), TP303.1
unnamed: J302.7, JP307.2 (B), TP312.1
unnamed: J302.8, JP308.2 (B), TP313.1
unnamed: J302.9, JP309.2 (B), TP314.1
unnamed: J401.1, RN401.4, TP402.1, U401.11 (T1IN)
unnamed: J401.2, RN401.3, TP404.1, U401.10 (T2IN)
unnamed: J401.3, RN401.2, TP406.1, U401.12 (R1OUT)
unnamed: J401.4, RN401.1 (4), TP408.1, U401.9 (R2OUT)
unnamed: J402.1, JP401.2 (B), TP401.1
unnamed: J402.2, JP402.2 (B), TP403.1
unnamed: J402.7, JP407.2 (B), TP412.1
unnamed: J402.8, JP408.2 (B), TP413.1
unnamed: J402.9, JP409.2 (B), TP414.1
unnamed: J501.1, RN501.4, TP502.1, U501.11 (T1IN)
unnamed: J501.2, RN501.3, TP504.1, U501.10 (T2IN)
unnamed: J501.3, RN501.2, TP506.1, U501.12 (R1OUT)
unnamed: J501.4, RN501.1 (4), TP508.1, U501.9 (R2OUT)
unnamed: J502.1, JP501.2 (B), TP501.1
unnamed: J502.2, JP502.2 (B), TP503.1
unnamed: J502.7, JP507.2 (B), TP512.1
unnamed: J502.8, JP508.2 (B), TP513.1
unnamed: J502.9, JP509.2 (B), TP514.1
unnamed: C304.1, U301.1 (C1+)
unnamed: C304.2, U301.3 (C1-)
unnamed: C306.1, U301.4 (C2+)
unnamed: C306.2, U301.5 (C2-)
unnamed: C303.2, U301.2 (VS+)
unnamed: C305.1, U301.6 (VS-)
unnamed: C404.1, U401.1 (C1+)
unnamed: C404.2, U401.3 (C1-)
unnamed: C406.1, U401.4 (C2+)
unnamed: C406.2, U401.5 (C2-)
unnamed: C403.2, U401.2 (VS+)
unnamed: C405.1, U401.6 (VS-)
unnamed: C504.1, U501.1 (C1+)
unnamed: C504.2, U501.3 (C1-)
unnamed: C506.1, U501.4 (C2+)
unnamed: C506.2, U501.5 (C2-)
unnamed: C503.2, U501.2 (VS+)
unnamed: C505.1, U501.6 (VS-)

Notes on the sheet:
RXD: Serial Data from Transceiver to Computer ~{CTS}: Used by Transceiver to inhibit Computer from transitting serial data TXD: Serial Data from Computer to Transceiver ~{RTS}: Used by Computer to inhibit Transceiver from transmitting serial data
Output: Protect against any voltages greater than +-15V Input: Protect against any voltages greater than +-25V
